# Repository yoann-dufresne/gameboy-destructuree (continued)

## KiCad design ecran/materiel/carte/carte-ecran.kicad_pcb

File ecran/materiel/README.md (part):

# Matériel de l'écran 3 × 3 — le montage définitif

*Conçu le 29/10/2026.* L'écran fonctionne ; son montage de preuve de concept a fait son
office. Ce dossier le remplace par un montage qu'on peut poser à plat sur le sol, mettre
debout sur une table, accrocher au mur, et dépanner sans démonter : **une carte** où s'enfichent les quatre Pico et toutes les
nappes, **un cadre** en profilés aluminium 2020 et pièces imprimées, **un faisceau**
d'alimentation propre, du secteur à chaque dalle.

**État : conçu et vérifié par calcul ; cartes reçues de JLCPCB le 05/11/2026, à monter.** La
carte passe les contrôles électriques de KiCad sans une erreur ; le cadre passe ses contrôles
d'interférences et d'accès. Ce qui reste à vérifier sur pièce est listé au [§8](#8-limites-et-points-à-vérifier).
Le montage de la carte, étape par étape et éprouvé à chaque étape :
[`montage-carte.md`](montage-carte.md).

**Ce qu'il faut acheter : [`liste-materiel.md`](liste-materiel.md)**, de l'ordre de 250 à
350 €, hors dalles, Pico et alimentation, déjà là.

---

## 1. Ce qui change

| Sur le montage de preuve de concept | Dans le montage définitif |
|---|---|
| Les dalles s'affaissent : des plaques de PLA les tiennent entre elles, et le PLA flue sous le poids | Chaque rangée est vissée sur un **profilé aluminium 2020**, et les trois profilés sur **deux montants 2020**. L'aluminium porte, le plastique ne fait plus que relier |
| Des fils volants au dos | **Une carte** : les 4 Pico sur supports, les liaisons tête → nœuds en pistes, les tampons de niveaux, les 3 embases HUB75, les 9 départs d'alimentation |
| Plusieurs cosses écrasées ensemble sur chaque borne de l'alimentation | **Un câble par dalle**, protégé par **son fusible** et débrochable à la carte ; de l'alimentation à la carte, **quatre fils de 2,5 mm², un par borne** |
| Les Pico alimentés par USB | Les Pico **tirent leur 5 V du même bus**, à travers un fusible réarmable, une ferrite et une diode Schottky par Pico. L'USB reste branchable pour flasher : aucun des deux n'alimente l'autre |
| Ni pied ni accroche | **Quatre patins arrière**, toujours en place : l'écran se pose **à plat sur le sol**, LED vers le haut, ou s'accroche au mur par **deux crochets** à trou de serrure. **Deux pieds** amovibles le tiennent debout sur une table, droit ou penché de 10° |
| Les connecteurs des dalles difficiles à atteindre | **Rien** — cadre, carte, alimentation, câbles — au-dessus d'un connecteur de dalle ni à moins de 8 mm, jusqu'au plan du mur. Le générateur du cadre le vérifie à chaque exécution |

Le firmware ne change pas d'une ligne : la carte reprend les brochages des `config.h` de
la tête et des nœuds.

---

## 2. Vue d'ensemble

Vue de dos, flèches des dalles vers le haut, numérotation du cadre v3 :

```
   7 8 9   ← nœud 0 (U2), nappe J4 → entrée de la dalle 7      crochets muraux sur ce profilé
   4 5 6   ← nœud 1 (U3), nappe J5 → dalle 4   ┐ la carte, sur les dalles 4 et 5
   1 2 3   ← nœud 2 (U4), nappe J6 → dalle 1   ┘ l'alimentation, sur le profilé du bas
           4 patins arrière au bout des montants ; pieds de table sous le profilé du bas ;
           prise secteur à gauche
```

| | |
|---|---|
| Encombrement | 576 × 576 mm ; 120 mm de la face des LED au sol, ou au mur |
| À plat sur le sol | sur les 4 patins arrière, rectangle d'appui de 384 × 340 mm ; centre de gravité à 131 mm de son bord |
| Debout, sur une table | écran à 25 mm de la table ; patins des pieds de 240 mm, qui dépassent de 35 mm devant |
| Masse | environ 7,5 kg, estimée pièce par pièce : dalles ≈ 4,5 kg, alimentation ≈ 0,7 kg, cadre et carte ≈ 2,3 kg |
| Alimentation | une seule, **5 V 30 A**, sur le profilé du bas ; secteur par une embase IEC à interrupteur et fusible |

---

## 3. La carte — [`carte/`](carte/)

**198 × 135 mm, 2 couches, cuivre 2 oz.** Elle se visse sur un plateau imprimé, lui-même
vissé au profilé de la rangée du milieu, une patte appuyée contre le montant gauche.

| Repère | Rôle |
|---|---|
| **J1** | entrée 5 V 30 A, bornier à vis : bornes 1-2 = +5 V, 3-4 = masse. Deux fils de 2,5 mm² par polarité |
| **F1–F9, J11–J19** | les 9 départs, un par dalle : fusible lame mini **7,5 A** et fiche débrochable au pas de 5,08 mm. Repérés D1 à D9 sur la sérigraphie |
| LED11–LED19 | voyant rouge d'un départ : **allumé = fusible fondu**, dalle branchée |
| LED1 | voyant vert : le 5 V est là |
| **U1** | la tête, Pico 2 W, USB en haut, antenne au bord bas de la carte, sans cuivre dessous |
| **U2–U4** | les nœuds 0, 1 et 2 (rangées du haut, du milieu, du bas), Pico 2, USB à droite |
| **J4, J5, J6** | embases HUB75 vers l'entrée des dalles 7, 4 et 1 |
| U5–U10 | deux tampons **74AHCT541** par nœud, alimentés en 5 V : niveaux 5 V vers les dalles, Pico protégés. Leurs entrées n'ont pas de diode vers l'alimentation : un nœud branché en USB, bus éteint, ne réalimente pas la carte. Validés par le 3V3 de leur Pico (Q1–Q3) : **sans Pico, la rangée reste noire**, même tête en marche |
| JP1–JP3 | G1 de chaque nœud : cavalier sur 1-2 = GP1, la normale ; sur 2-3 = GP15, pour un Pico dont la sortie GP1 est morte (journal du 29/10/2026) |
| SW1–SW4 | RESET de la tête et des trois nœuds |
| J7 | sonde pour analyseur logique : VSYNC, RDY0–2, GP17 et GP18 de chaque Pico, une masse par signal |
| J2, J3 | potentiomètre de luminosité sur GP26 de la tête (option, non lu par le firmware) ; broches libres de la tête |

- **Liaisons tête → nœuds** : en pistes, avec les résistances série de 33 Ω du [§2.6 du
  plan](../docs/plan-firmware.md). Les nappes IDC 10 points disparaissent.
- **5 V des Pico** : fusible réarmable 0,75 A, ferrite, condensateurs, puis une diode SS14
  vers le VSYS de chaque Pico.
- **Mesure du bus** : un pont diviseur ramène le 5 V à 2,5 V sur GP27 (ADC1) de la tête.
  Câblé, pas encore lu par le firmware.

**Fabrication** — tout est dans [`carte/fab/`](carte/fab/). Le zip ne contient que la
**carte nue**, Gerber et perçages. Le **peuplement** est dans deux fichiers à part, qu'on
téléverse à l'étape d'assemblage de la commande :

| Fichier | Usage |
|---|---|
| `carte-ecran-gerber.zip` | la carte nue, à déposer tel quel chez JLCPCB |
| `bom_jlcpcb.csv`, `cpl_jlcpcb.csv` | le peuplement : nomenclature, avec les codes LCSC, et placement des 93 CMS de la face dessus |
| `nomenclature.md` | toutes les pièces de la carte, CMS, traversants et vrac |
| `schema.pdf`, `plan_montage.pdf`, `cuivre_dessus.pdf`, `cuivre_dessous.pdf` | pour souder et dépanner |

**Commander chez JLCPCB :**

1. Déposer `carte-ecran-gerber.zip`. Options : 2 couches, 1,6 mm, **cuivre extérieur 2 oz**,
   HASL sans plomb, 5 cartes.
2. Activer **PCB Assembly**, face dessus, 2 cartes à peupler. Téléverser `bom_jlcpcb.csv`,
   puis `cpl_jlcpcb.csv`.
3. Vérifier que les 16 références LCSC sont reconnues et en stock, puis, dans l'aperçu,
   **l'orientation** des pièces polarisées : [`fab/orientation_cms.png`](carte/fab/orientation_cms.png)
   marque en rouge le repère de chacune (cathode des LED et des SS14, + de C4, broche 1 des
   74AHCT541, patte seule des 2N7002, cathode de D1). Les bibliothèques de JLCPCB ne tournent pas toutes
   comme celles de KiCad : `cpl_jlcpcb.csv` corrige déjà les TSSOP (+270°), les SOT-23 (+180°)
   et les réseaux de résistances (+90°), d'après l'aperçu du 29/10/2026. Dans l'aperçu, le
   point rose des 74AHCT541 doit tomber en bas à droite, contre le ◁ de la sérigraphie.
4. Les traversants n'en font pas partie : supports des Pico, embases HUB75, porte-fusibles,
   borniers, C1 et C2, boutons, barrettes. Ils s'achètent à part, au §1b de la
   [liste de matériel](liste-materiel.md), et se soudent à la main.

Contrôles passés : ERC sans erreur, netlist identique à la description, routage complet,
DRC sans violation, aucune connexion manquante, schéma et circuit concordants.

**Vérifications avant commande (29/10/2026)** :

| Point | Résultat |
|---|---|
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
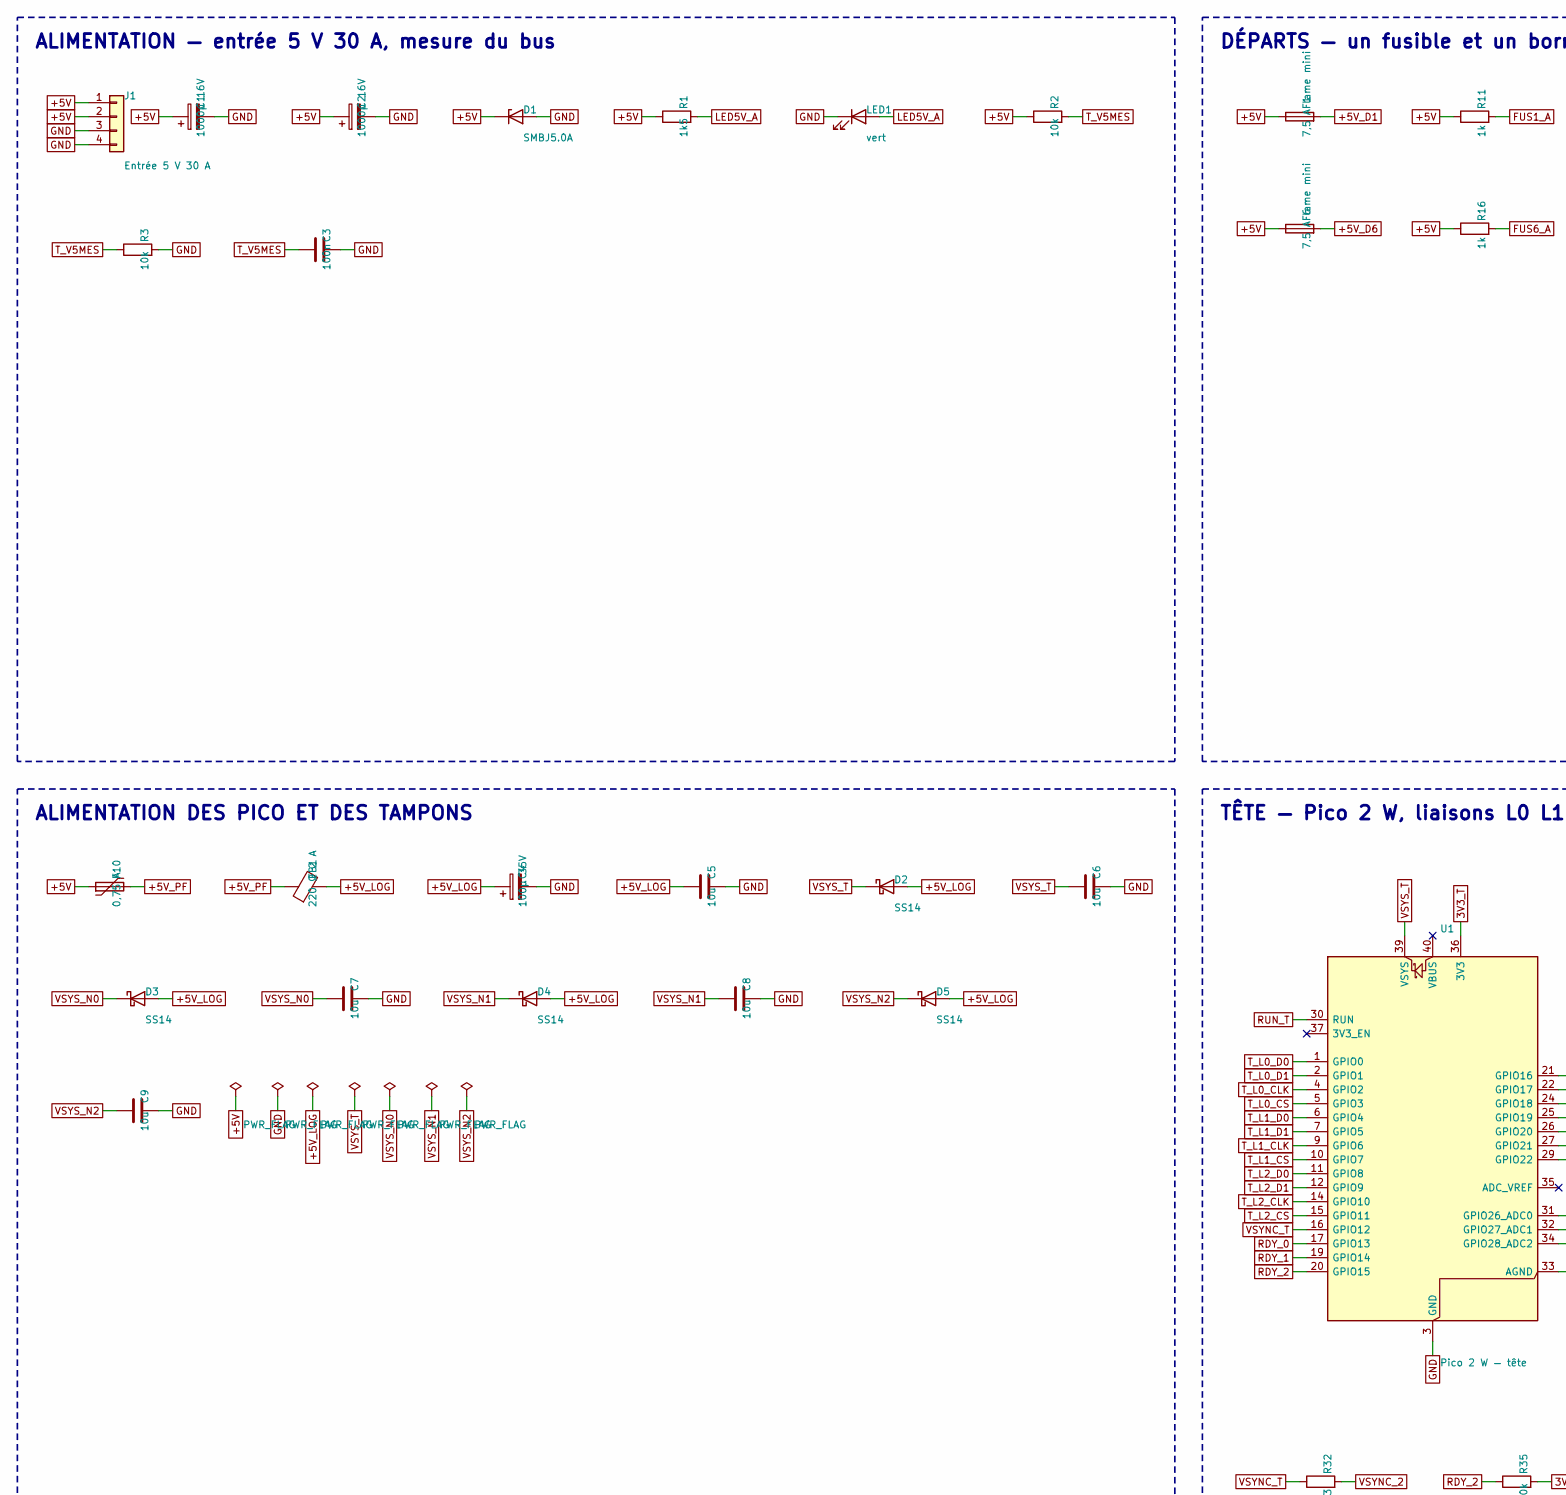
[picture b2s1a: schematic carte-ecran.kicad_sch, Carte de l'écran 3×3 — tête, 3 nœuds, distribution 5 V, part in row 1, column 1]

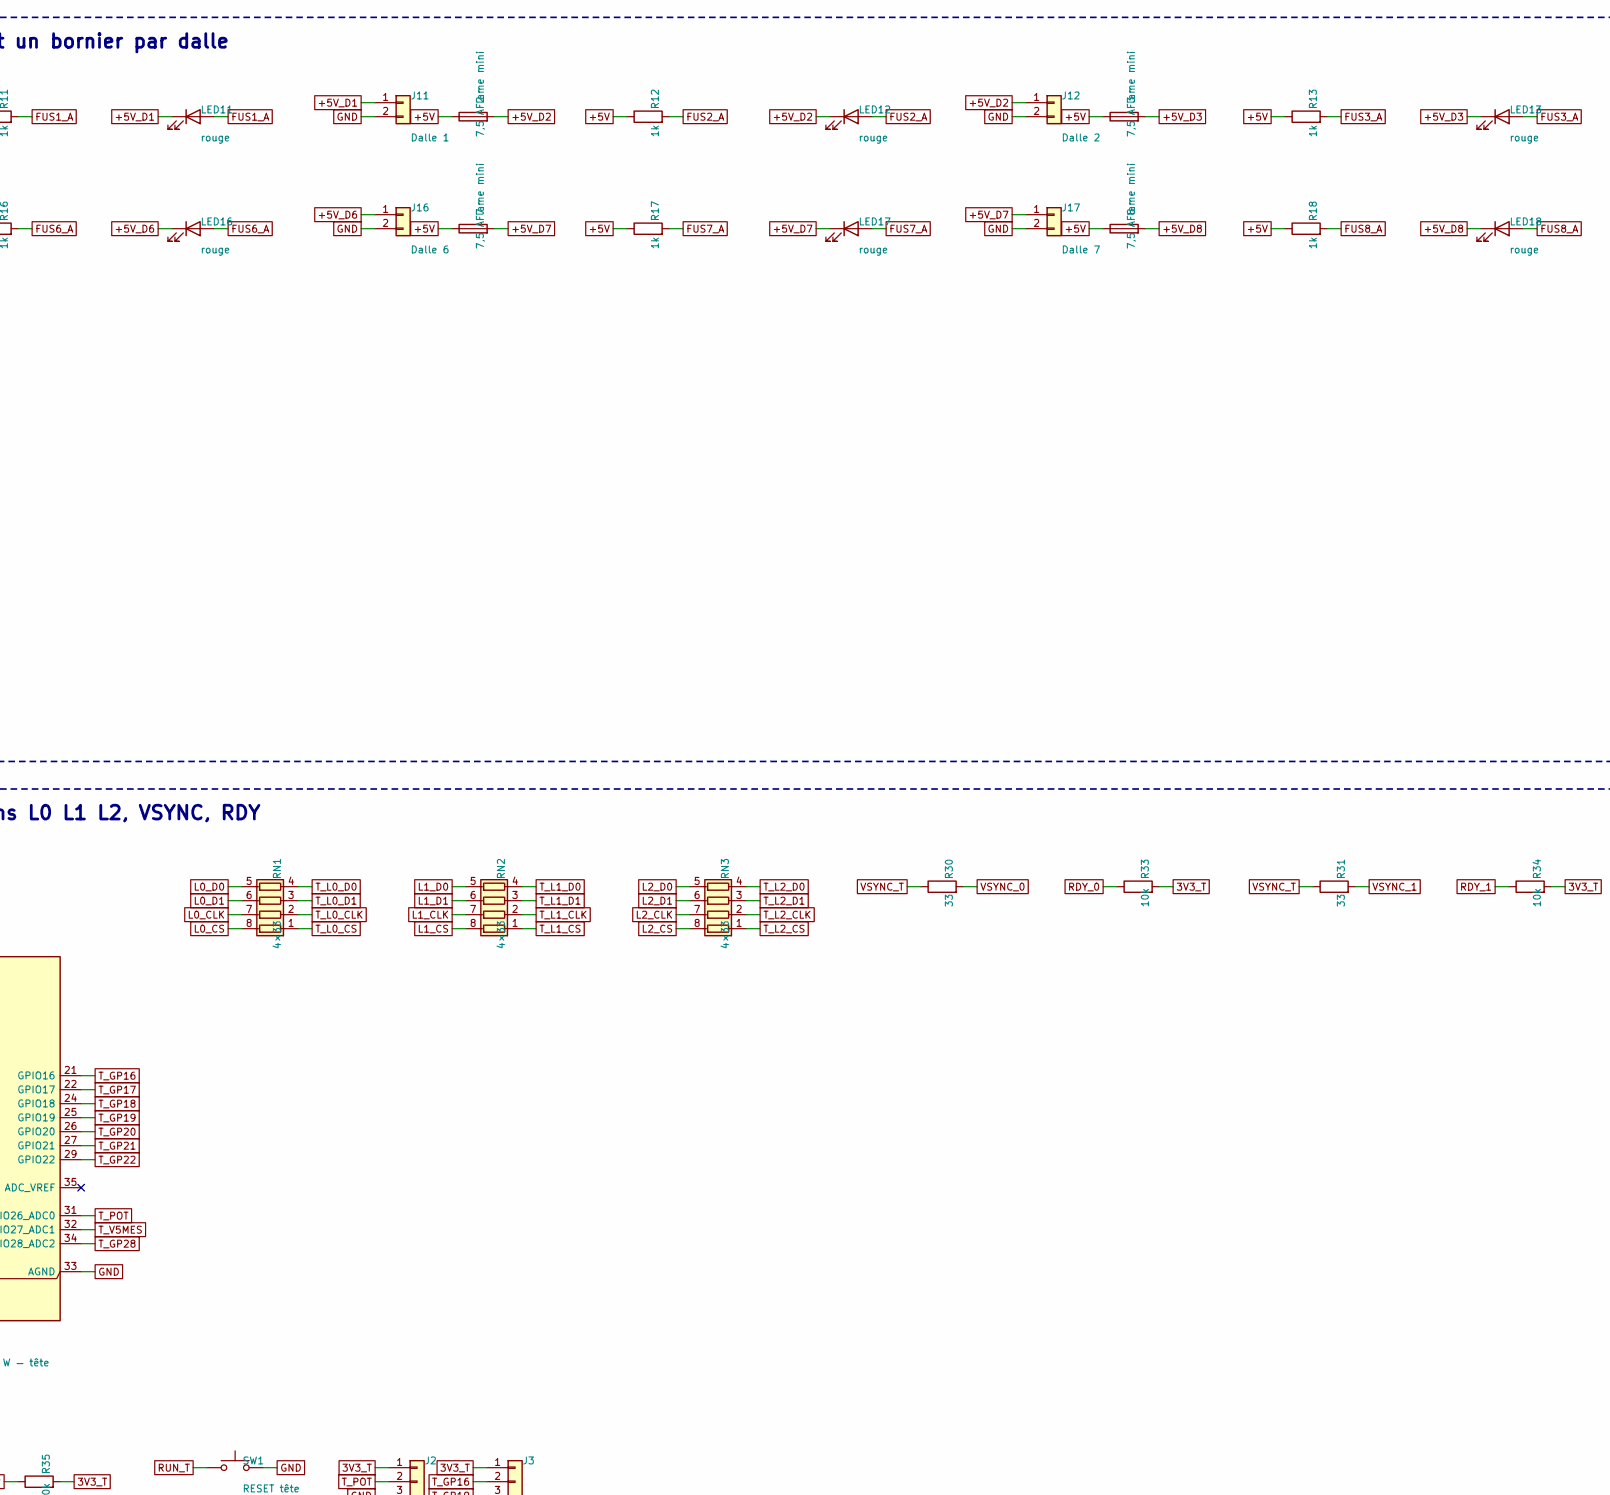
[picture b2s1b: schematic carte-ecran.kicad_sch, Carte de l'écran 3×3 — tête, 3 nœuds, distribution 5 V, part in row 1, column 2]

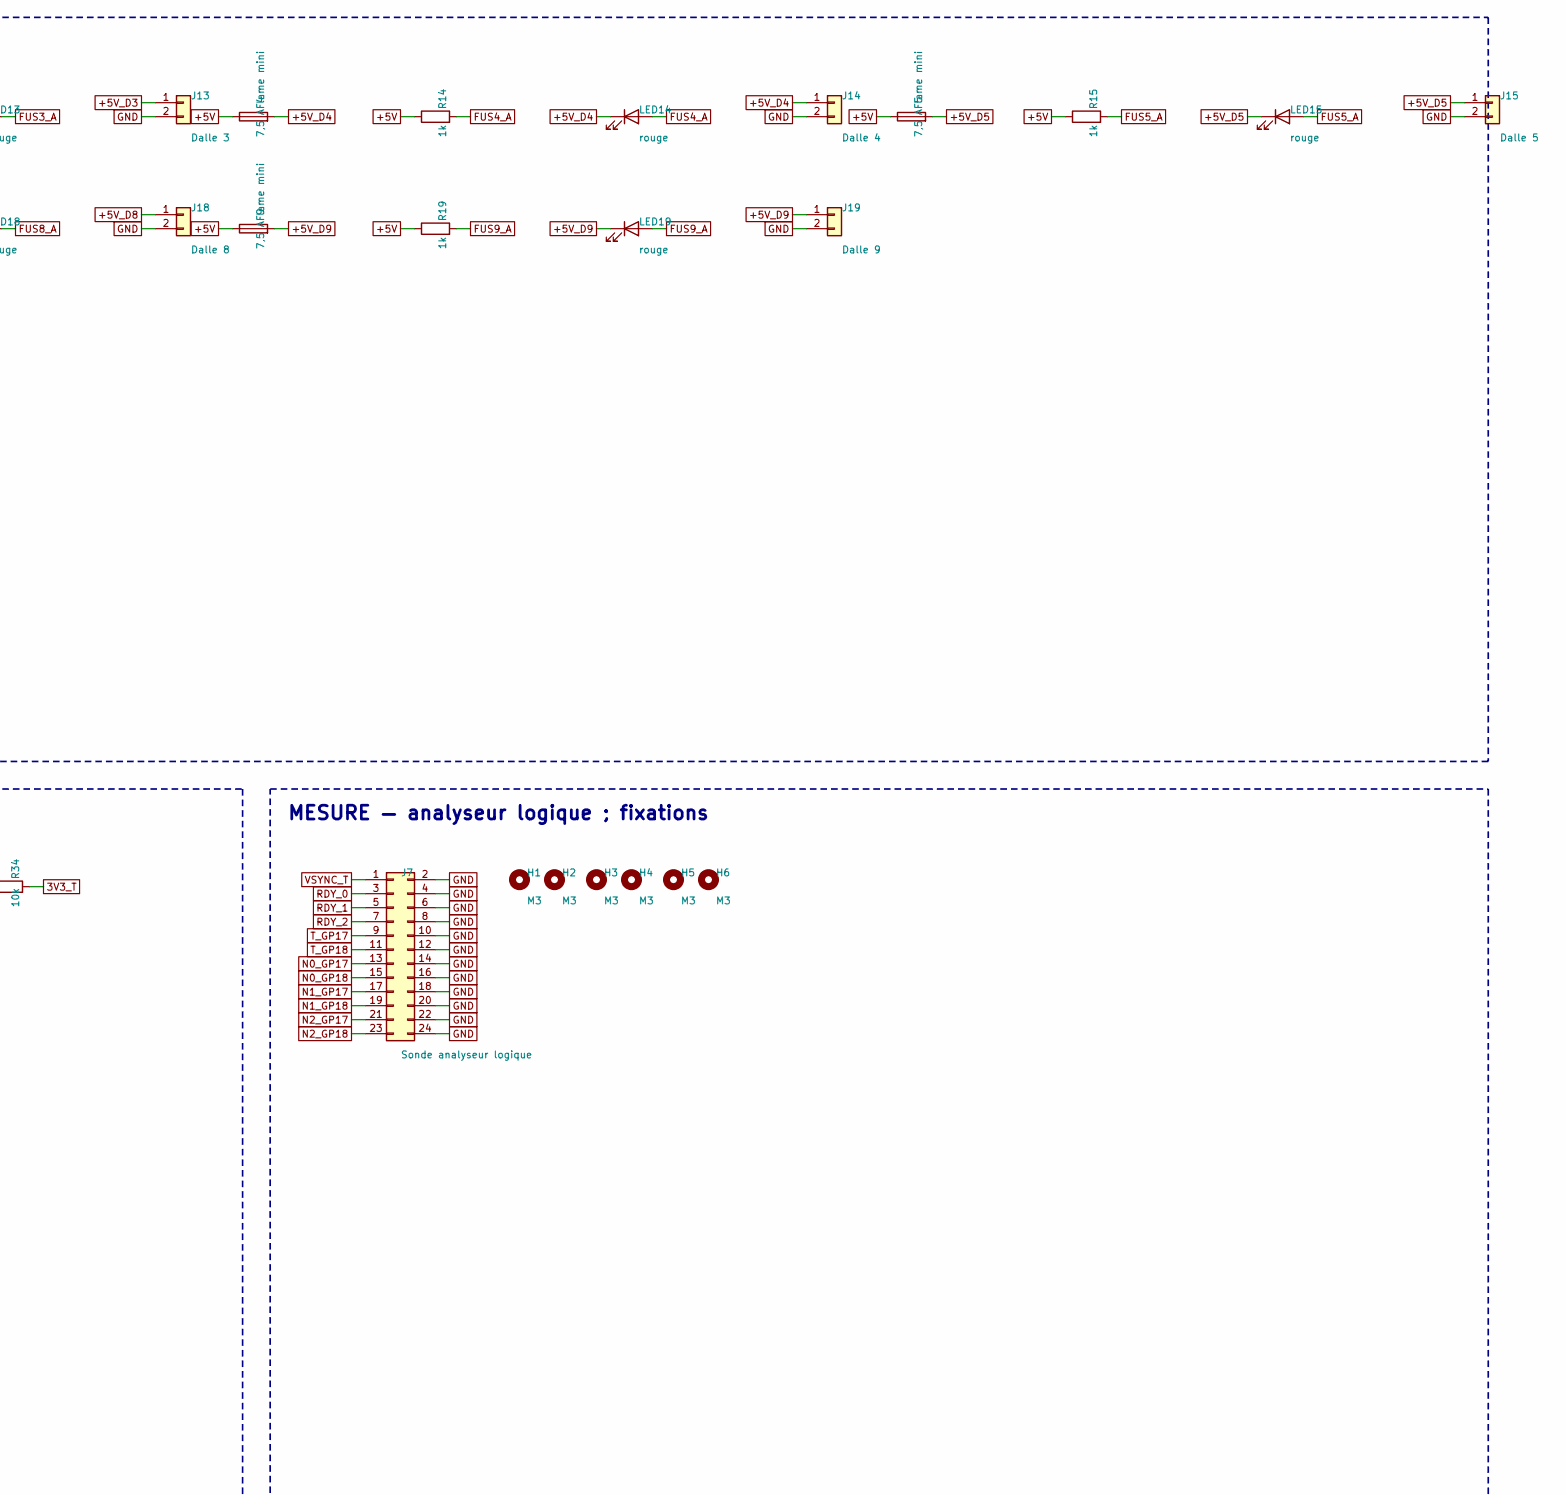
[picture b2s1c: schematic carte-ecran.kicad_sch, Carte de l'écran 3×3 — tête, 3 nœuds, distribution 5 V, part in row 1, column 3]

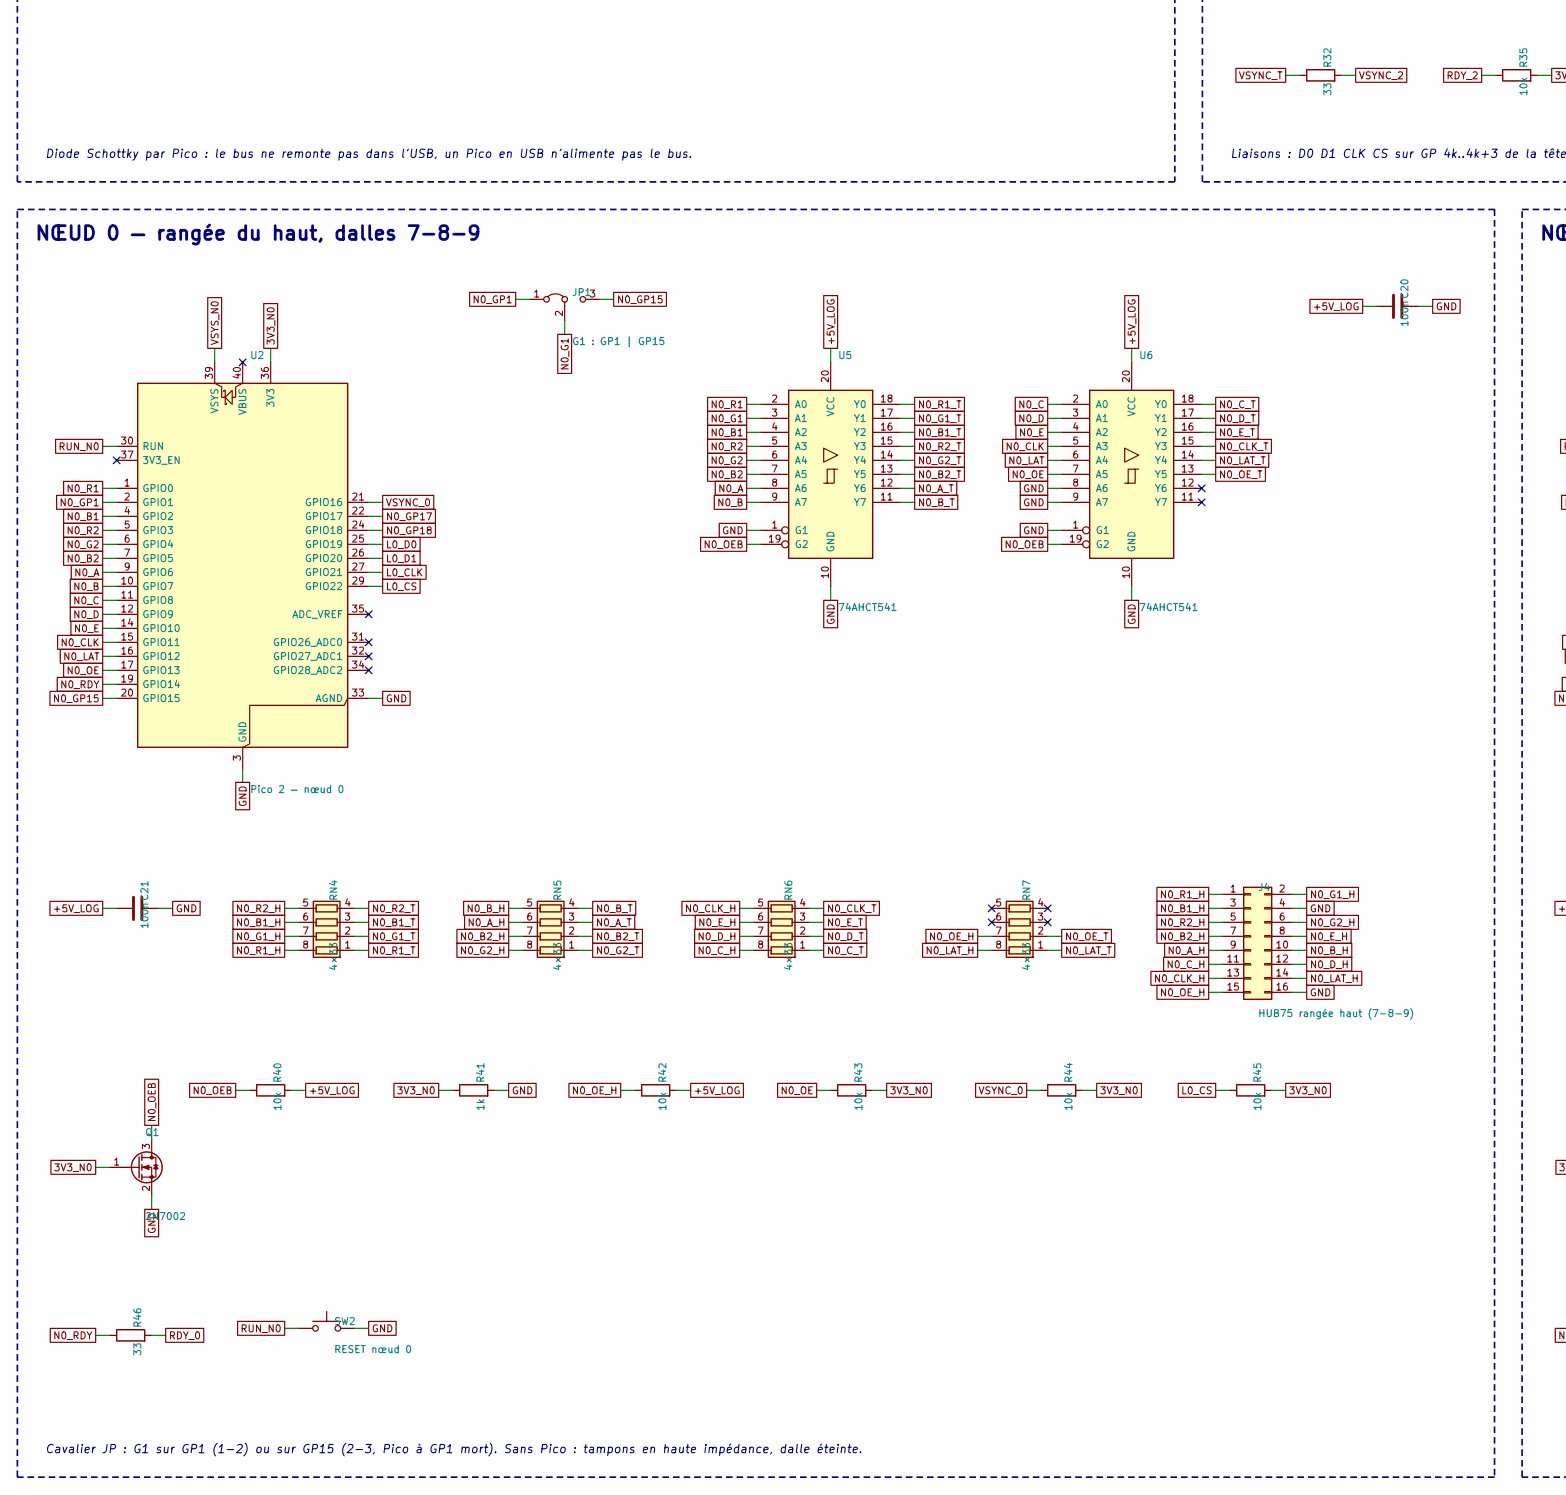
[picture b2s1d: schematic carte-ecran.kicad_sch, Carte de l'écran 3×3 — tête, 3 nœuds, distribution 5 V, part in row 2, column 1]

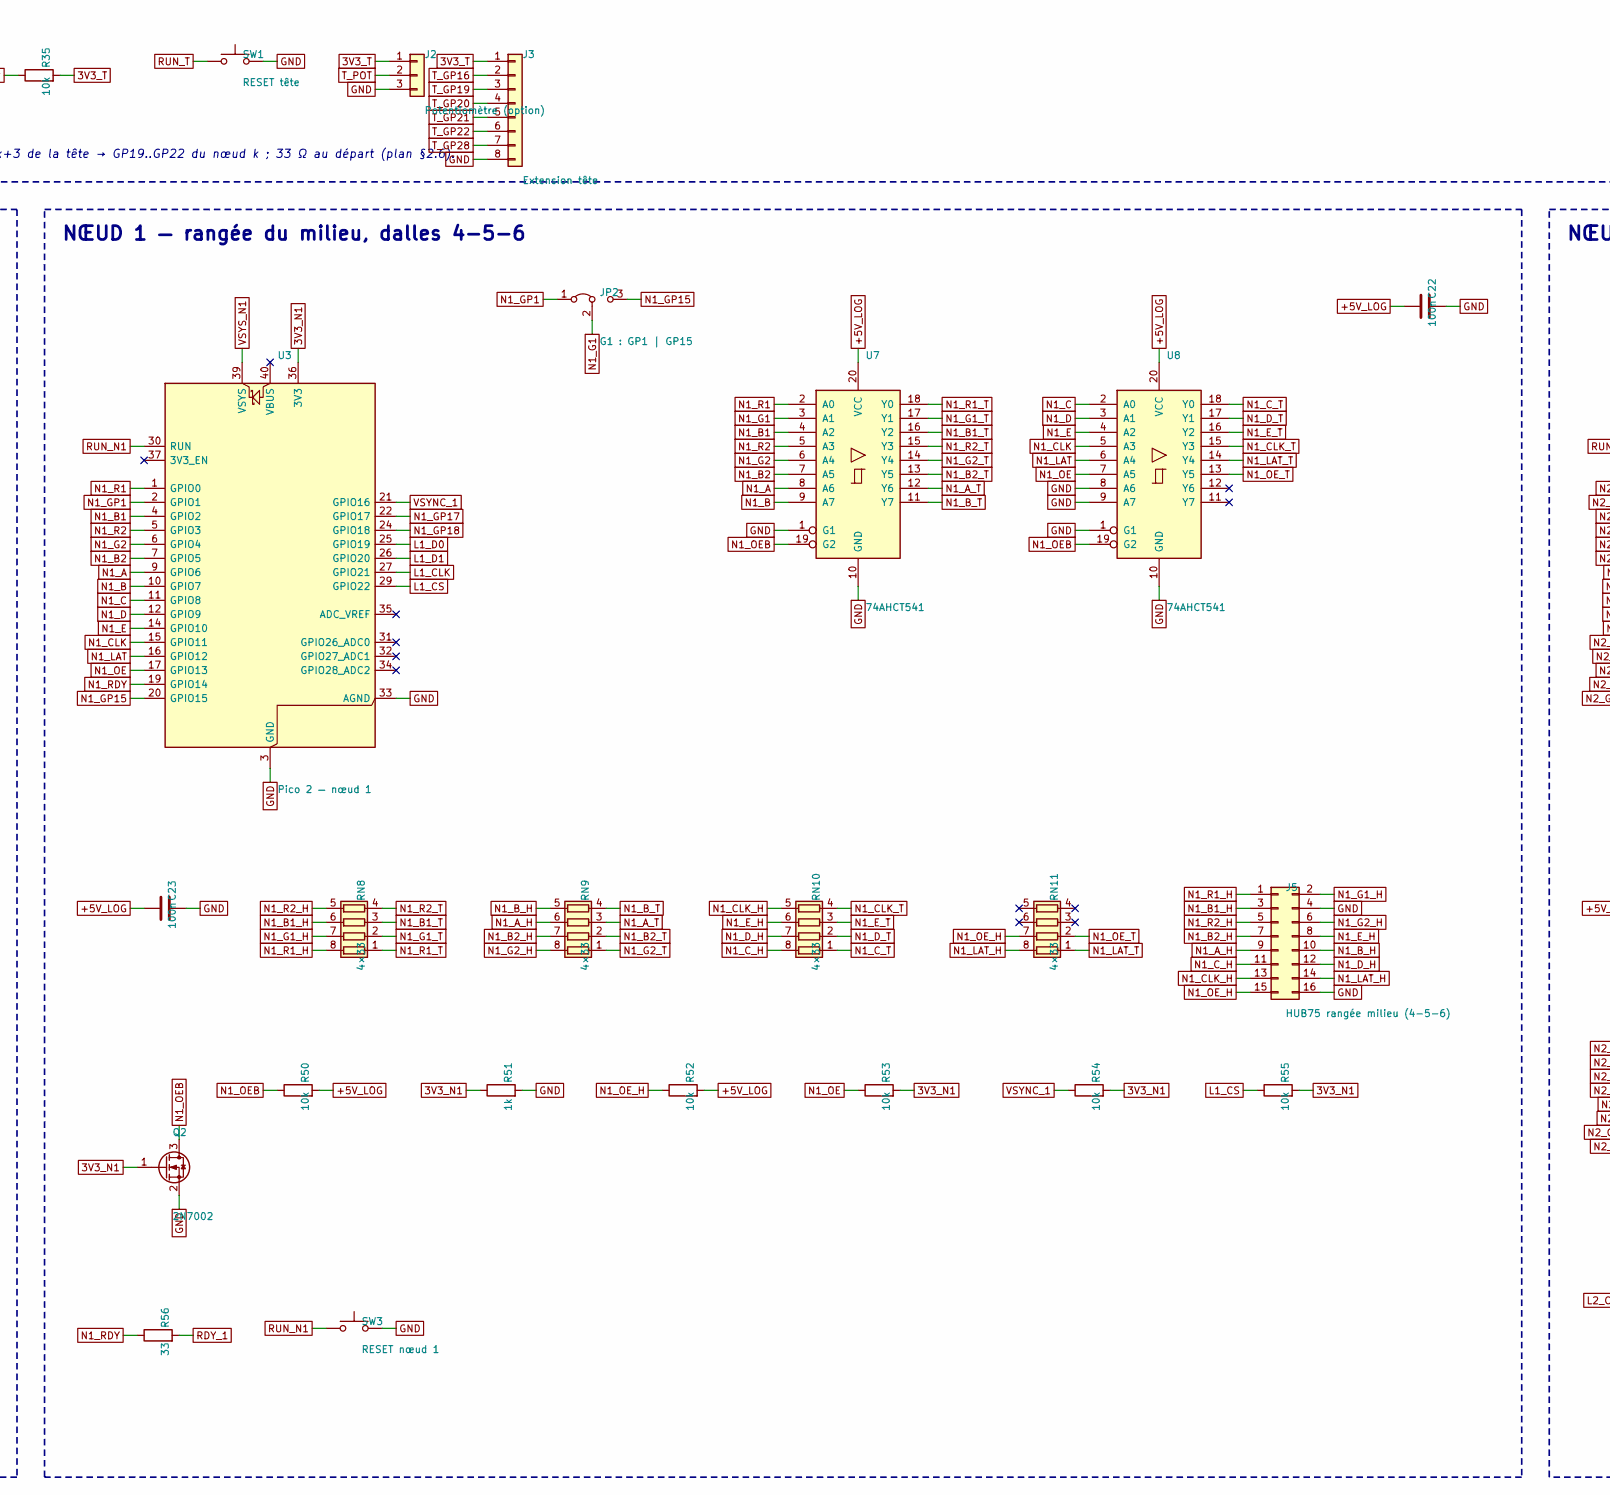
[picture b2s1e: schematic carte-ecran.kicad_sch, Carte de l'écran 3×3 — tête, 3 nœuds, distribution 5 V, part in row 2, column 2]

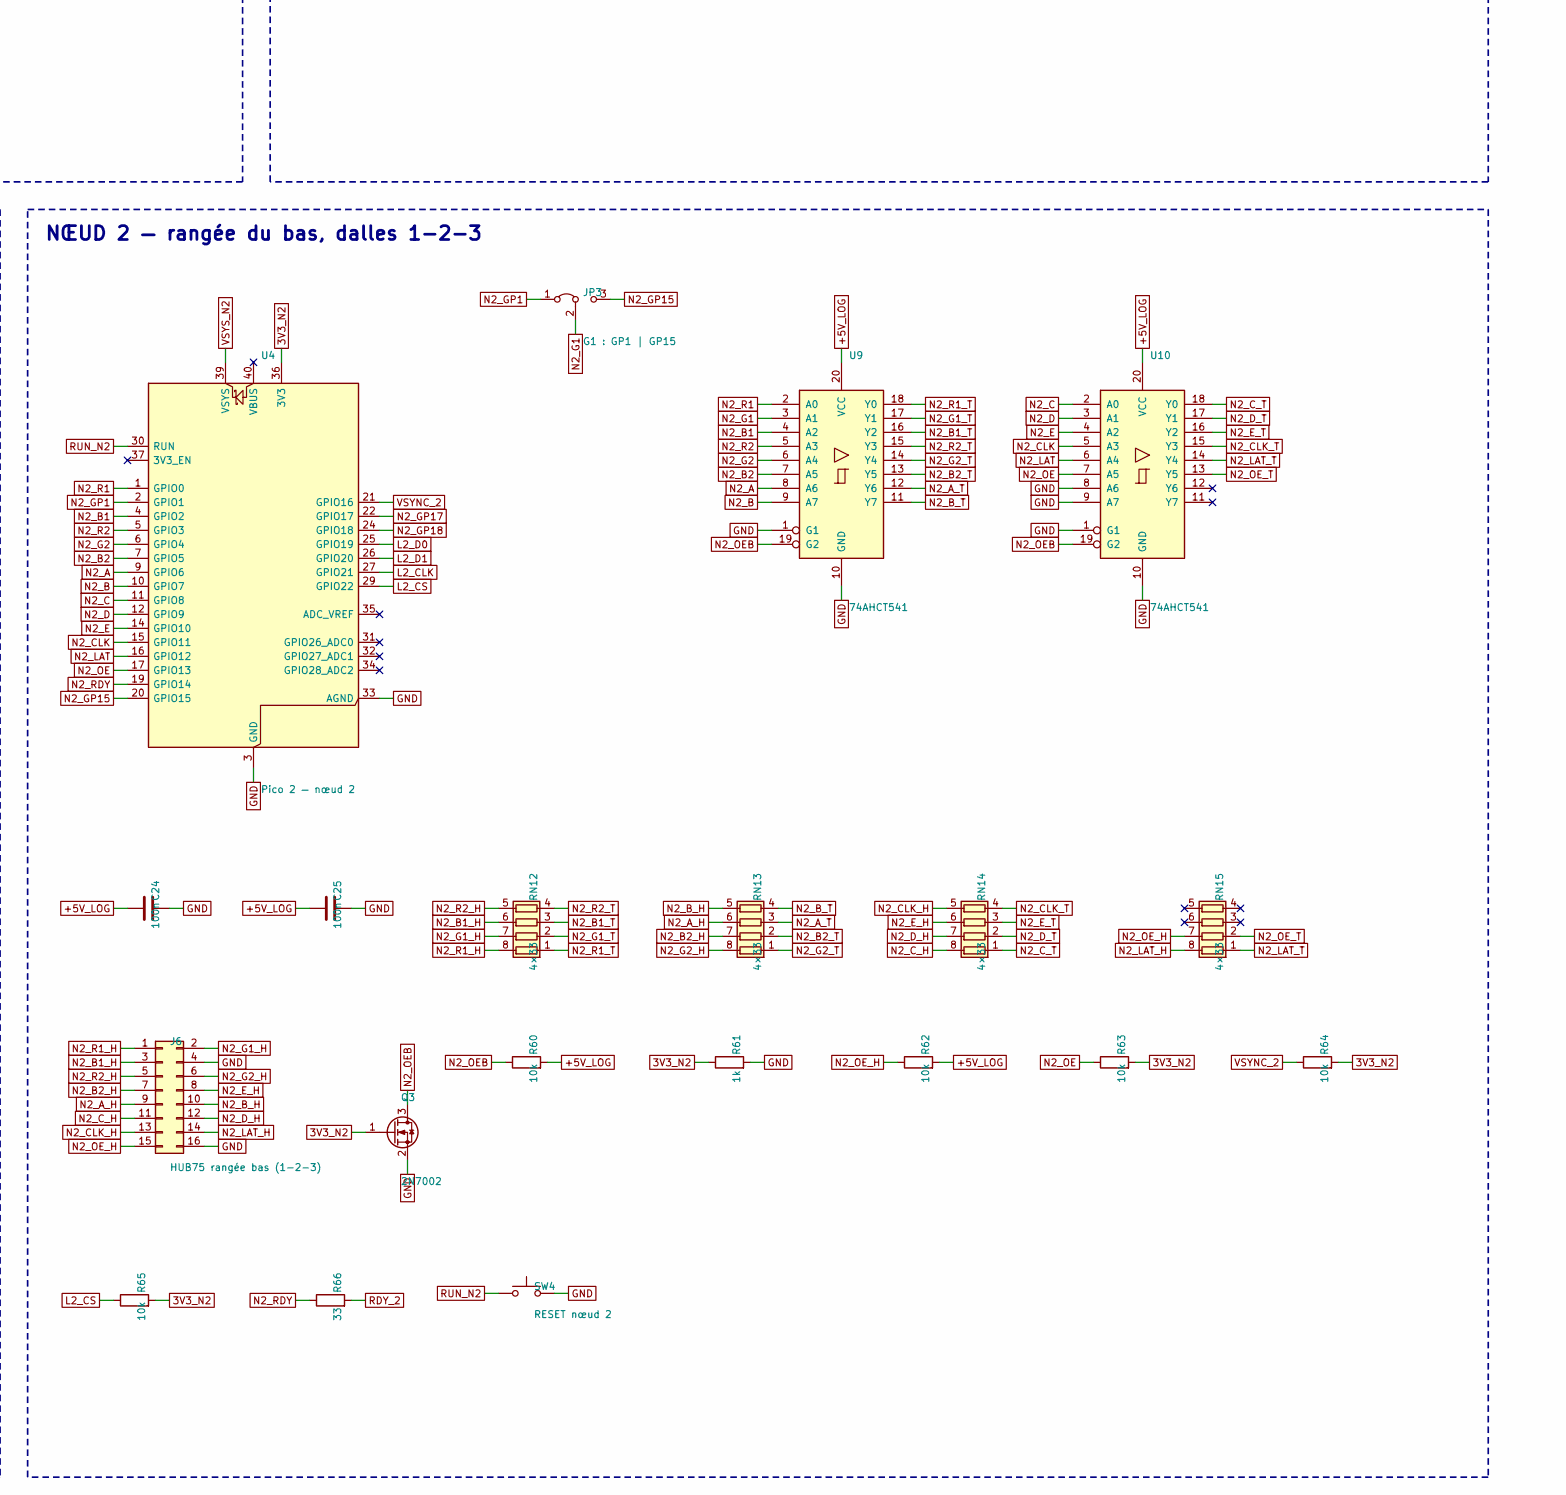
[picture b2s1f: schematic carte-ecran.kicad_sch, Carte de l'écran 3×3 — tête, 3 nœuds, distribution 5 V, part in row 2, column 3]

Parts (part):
C1, C2: 1000µ 16V; CP_Radial_D10.0mm_P5.00mm; MPN 1000 µF 16 V radial Ø10 × 20, pas de 5 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
C3, C20, C21, C22, C23, C24, C25: 100n; C_0603_1608Metric; MPN CC0603KRX7R9BB104; LCSC C14663
C4: 100µ 35V; CP_Elec_6.3x7.7; MPN CK1V101M-CRE77 (100 µF 35 V, 6,3×7,7); LCSC C19184138
C5, C6, C7, C8, C9: 10u; C_0805_2012Metric; MPN CL21A106KAYNNNE; LCSC C15850
D1: SMBJ5.0A; D_SMB; MPN SMBJ5.0A (Littelfuse, unidirectionnelle); LCSC C83333
D2, D3, D4, D5: SS14; D_SMA; MPN SS14; LCSC C2480
F1, F2, F3, F4, F5, F6, F7, F8, F9: 7,5 A lame mini; Fuseholder_Blade_Mini_Keystone_3568; MPN Keystone 3568 (porte-fusible lame mini 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
F10: 0,75 A; Fuse_1812_4532Metric; MPN 1812L075/33DR (Littelfuse, 0,75 A maint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; LCSC C151170
FB1: 220 Ω 2 A; L_0805_2012Metric; MPN BLM21PG221SN1D (220 Ω à 100 MHz, 2 A); LCSC C85840
H1, H2, H3, H4, H5, H6: M3; MountingHole_3.2mm_M3
J1: Entrée 5 V 30 A; TerminalBlock_Phoenix_MKDS-3-4-5.08_1x04_P5.08mm_Horizontal; MPN Phoenix MKDS 3/4-5,08 (1712805), 24 A p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
J2: Potentiomètre (option); PinHeader_1x03_P2.54mm_Vertical; MPN Barrette mâle 2,54 mm
J3: Extension tête; PinHeader_1x08_P2.54mm_Vertical; MPN Barrette mâle 2,54 mm
J4: HUB75 rangée haut (7-8-9); IDC-Header_2x08_P2.54mm_Vertical; MPN Embase IDC 2×8 détrompée, 2,54 mm, droi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
J5: HUB75 rangée milieu (4-5-6); IDC-Header_2x08_P2.54mm_Vertical; MPN Embase IDC 2×8 détrompée, 2,54 mm, droi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
J6: HUB75 rangée bas (1-2-3); IDC-Header_2x08_P2.54mm_Vertical; MPN Embase IDC 2×8 détrompée, 2,54 mm, droi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
J7: Sonde analyseur logique; PinHeader_2x12_P2.54mm_Vertical; MPN Barrette mâle 2,54 mm
J11: Dalle 1; PhoenixContact_MSTBA_2,5_2-G-5,08_1x02_P5.08mm_Horizontal; MPN Phoenix MSTBA 2,5/2-G-5,08 (1757242) + 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
J12: Dalle 2; PhoenixContact_MSTBA_2,5_2-G-5,08_1x02_P5.08mm_Horizontal; MPN Phoenix MSTBA 2,5/2-G-5,08 (1757242) + 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
J13: Dalle 3; PhoenixContact_MSTBA_2,5_2-G-5,08_1x02_P5.08mm_Horizontal; MPN Phoenix MSTBA 2,5/2-G-5,08 (1757242) + 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
J14: Dalle 4; PhoenixContact_MSTBA_2,5_2-G-5,08_1x02_P5.08mm_Horizontal; MPN Phoenix MSTBA 2,5/2-G-5,08 (1757242) + 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
J15: Dalle 5; PhoenixContact_MSTBA_2,5_2-G-5,08_1x02_P5.08mm_Horizontal; MPN Phoenix MSTBA 2,5/2-G-5,08 (1757242) + 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
J16: Dalle 6; PhoenixContact_MSTBA_2,5_2-G-5,08_1x02_P5.08mm_Horizontal; MPN Phoenix MSTBA 2,5/2-G-5,08 (1757242) + 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
J17: Dalle 7; PhoenixContact_MSTBA_2,5_2-G-5,08_1x02_P5.08mm_Horizontal; MPN Phoenix MSTBA 2,5/2-G-5,08 (1757242) + 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
J18: Dalle 8; PhoenixContact_MSTBA_2,5_2-G-5,08_1x02_P5.08mm_Horizontal; MPN Phoenix MSTBA 2,5/2-G-5,08 (1757242) + 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
J19: Dalle 9; PhoenixContact_MSTBA_2,5_2-G-5,08_1x02_P5.08mm_Horizontal; MPN Phoenix MSTBA 2,5/2-G-5,08 (1757242) + 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
JP1, JP2, JP3: G1 : GP1 | GP15; PinHeader_1x03_P2.54mm_Vertical; MPN Barrette mâle 2,54 mm
LED1: vert; LED_0603_1608Metric; MPN XL-1608PGC-06 (XINGLIGHT, vert émeraude); LCSC C7371905
LED11, LED12, LED13, LED14, LED15, LED16, LED17, LED18, LED19: rouge; LED_0603_1608Metric; MPN KT-0603R; LCSC C2286
PF1, PF2, PF3, PF4, PF5, PF6, PF7: PWR_FLAG
Q1, Q2, Q3: 2N7002; SOT-23; MPN 2N7002; LCSC C8545
R1: 1k5; R_0603_1608Metric; MPN 0603WAF1501T5E; LCSC C22843
R2, R3, R33, R34, R35, R40, R42, R43, R44, R45, R50, R52, R53, R54, R55, R60, R62, R63, R64, R65: 10k; R_0603_1608Metric; MPN 0603WAF1002T5E; LCSC C25804
R11, R12, R13, R14, R15, R16, R17, R18, R19, R41, R51, R61: 1k; R_0603_1608Metric; MPN 0603WAF1001T5E; LCSC C21190
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
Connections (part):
3V3_N0: Q1.1 (G), R41.1, R43.2, R44.2, R45.2, U2.36 (3V3)
3V3_N1: Q2.1 (G), R51.1, R53.2, R54.2, R55.2, U3.36 (3V3)
3V3_N2: Q3.1 (G), R61.1, R63.2, R64.2, R65.2, U4.36 (3V3)
3V3_T: J2.1, J3.1, R33.2, R34.2, R35.2, U1.36 (3V3)
+5V: C1.1, C2.1, D1.1 (K), F1.1, F2.1, F3.1, F4.1, F5.1, F6.1, F7.1, F8.1, F9.1, F10.1, J1.1, J1.2, PF1.1, R1.1, R2.1, R11.1, R12.1, R13.1, R14.1, R15.1, R16.1, R17.1, R18.1, R19.1
+5V_D1: F1.2, J11.1, LED11.1 (K)
+5V_D2: F2.2, J12.1, LED12.1 (K)
+5V_D3: F3.2, J13.1, LED13.1 (K)
+5V_D4: F4.2, J14.1, LED14.1 (K)
+5V_D5: F5.2, J15.1, LED15.1 (K)
+5V_D6: F6.2, J16.1, LED16.1 (K)
+5V_D7: F7.2, J17.1, LED17.1 (K)
+5V_D8: F8.2, J18.1, LED18.1 (K)
+5V_D9: F9.2, J19.1, LED19.1 (K)
+5V_LOG: C4.1, C5.1, C20.1, C21.1, C22.1, C23.1, C24.1, C25.1, D2.2 (A), D3.2 (A), D4.2 (A), D5.2 (A), FB1.2, PF3.1, R40.2, R42.2, R50.2, R52.2, R60.2, R62.2, U5.20 (VCC), U6.20 (VCC), U7.20 (VCC), U8.20 (VCC), U9.20 (VCC), U10.20 (VCC)
+5V_PF: F10.2, FB1.1
FUS1_A: LED11.2 (A), R11.2
FUS2_A: LED12.2 (A), R12.2
FUS3_A: LED13.2 (A), R13.2
FUS4_A: LED14.2 (A), R14.2
FUS5_A: LED15.2 (A), R15.2
FUS6_A: LED16.2 (A), R16.2
FUS7_A: LED17.2 (A), R17.2
FUS8_A: LED18.2 (A), R18.2
FUS9_A: LED19.2 (A), R19.2
GND: C1.2, C2.2, C3.2, C4.2, C5.2, C6.2, C7.2, C8.2, C9.2, C20.2, C21.2, C22.2, C23.2, C24.2, C25.2, D1.2 (A), J1.3, J1.4, J2.3, J3.8, J4.4, J4.16, J5.4, J5.16, J6.4, J6.16, J7.2, J7.4, J7.6, J7.8, J7.10, J7.12, J7.14, J7.16, J7.18, J7.20, J7.22, J7.24, J11.2, J12.2, J13.2, J14.2, J15.2, J16.2, J17.2, J18.2, J19.2, LED1.1 (K), PF2.1, Q1.2 (S), Q2.2 (S), Q3.2 (S), R3.2, R41.2, R51.2, R61.2, SW1.2, SW2.2, SW3.2, SW4.2, U1.3 (GND), U1.8 (GND), U1.13 (GND), U1.18 (GND), U1.23 (GND), U1.28 (GND), U1.33 (AGND), U1.38 (GND), U2.3 (GND), U2.8 (GND), U2.13 (GND), U2.18 (GND), U2.23 (GND), U2.28 (GND), U2.33 (AGND), U2.38 (GND), U3.3 (GND), U3.8 (GND), U3.13 (GND), U3.18 (GND)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
L0_CLK: RN1.7 (R2.2), U2.27 (GPIO21)
L0_CS: R45.1, RN1.8 (R1.2), U2.29 (GPIO22)
L0_D0: RN1.5 (R4.2), U2.25 (GPIO19)
L0_D1: RN1.6 (R3.2), U2.26 (GPIO20)
L1_CLK: RN2.7 (R2.2), U3.27 (GPIO21)
L1_CS: R55.1, RN2.8 (R1.2), U3.29 (GPIO22)
L1_D0: RN2.5 (R4.2), U3.25 (GPIO19)
L1_D1: RN2.6 (R3.2), U3.26 (GPIO20)
L2_CLK: RN3.7 (R2.2), U4.27 (GPIO21)
L2_CS: R65.1, RN3.8 (R1.2), U4.29 (GPIO22)
L2_D0: RN3.5 (R4.2), U4.25 (GPIO19)
L2_D1: RN3.6 (R3.2), U4.26 (GPIO20)
LED5V_A: LED1.2 (A), R1.2
N0_A: U2.9 (GPIO6), U5.8 (A6)
N0_A_H: J4.9, RN5.6 (R3.2)
N0_A_T: RN5.3 (R3.1), U5.12 (Y6)
N0_B: U2.10 (GPIO7), U5.9 (A7)
N0_B1: U2.4 (GPIO2), U5.4 (A2)
N0_B1_H: J4.3, RN4.6 (R3.2)
N0_B1_T: RN4.3 (R3.1), U5.16 (Y2)
N0_B2: U2.7 (GPIO5), U5.7 (A5)
N0_B2_H: J4.7, RN5.7 (R2.2)
N0_B2_T: RN5.2 (R2.1), U5.13 (Y5)
N0_B_H: J4.10, RN5.5 (R4.2)
N0_B_T: RN5.4 (R4.1), U5.11 (Y7)
N0_C: U2.11 (GPIO8), U6.2 (A0)
N0_CLK: U2.15 (GPIO11), U6.5 (A3)
N0_CLK_H: J4.13, RN6.5 (R4.2)
N0_CLK_T: RN6.4 (R4.1), U6.15 (Y3)
N0_C_H: J4.11, RN6.8 (R1.2)
N0_C_T: RN6.1 (R1.1), U6.18 (Y0)
N0_D: U2.12 (GPIO9), U6.3 (A1)
N0_D_H: J4.12, RN6.7 (R2.2)
N0_D_T: RN6.2 (R2.1), U6.17 (Y1)
N0_E: U2.14 (GPIO10), U6.4 (A2)
N0_E_H: J4.8, RN6.6 (R3.2)
N0_E_T: RN6.3 (R3.1), U6.16 (Y2)
N0_G1: JP1.2 (C), U5.3 (A1)
N0_G1_H: J4.2, RN4.7 (R2.2)
N0_G1_T: RN4.2 (R2.1), U5.17 (Y1)
N0_G2: U2.6 (GPIO4), U5.6 (A4)
N0_G2_H: J4.6, RN5.8 (R1.2)
N0_G2_T: RN5.1 (R1.1), U5.14 (Y4)
N0_GP1: JP1.1 (A), U2.2 (GPIO1)
N0_GP15: JP1.3 (B), U2.20 (GPIO15)
N0_GP17: J7.13, U2.22 (GPIO17)
N0_GP18: J7.15, U2.24 (GPIO18)
N0_LAT: U2.16 (GPIO12), U6.6 (A4)
N0_LAT_H: J4.14, RN7.8 (R1.2)
N0_LAT_T: RN7.1 (R1.1), U6.14 (Y4)
N0_OE: R43.1, U2.17 (GPIO13), U6.7 (A5)
N0_OEB: Q1.3 (D), R40.1, U5.19 (G2), U6.19 (G2)
N0_OE_H: J4.15, R42.1, RN7.7 (R2.2)
N0_OE_T: RN7.2 (R2.1), U6.13 (Y5)
N0_R1: U2.1 (GPIO0), U5.2 (A0)
N0_R1_H: J4.1, RN4.8 (R1.2)
N0_R1_T: RN4.1 (R1.1), U5.18 (Y0)
N0_R2: U2.5 (GPIO3), U5.5 (A3)
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
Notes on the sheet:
ALIMENTATION — entrée 5 V 30 A, mesure du bus
DÉPARTS — un fusible et un bornier par dalle
ALIMENTATION DES PICO ET DES TAMPONS
TÊTE — Pico 2 W, liaisons L0 L1 L2, VSYNC, RDY
MESURE — analyseur logique ; fixations
NŒUD 0 — rangée du haut, dalles 7-8-9
NŒUD 1 — rangée du milieu, dalles 4-5-6
NŒUD 2 — rangée du bas, dalles 1-2-3
Liaisons : D0 D1 CLK CS sur GP 4k..4k+3 de la tête → GP19..GP22 du nœud k ; 33 Ω au départ (plan §2.6).
Diode Schottky par Pico : le bus ne remonte pas dans l'USB, un Pico en USB n'alimente pas le bus.
Cavalier JP : G1 sur GP1 (1-2) ou sur GP15 (2-3, Pico à GP1 mort). Sans Pico : tampons en haute impédance, dalle éteinte.

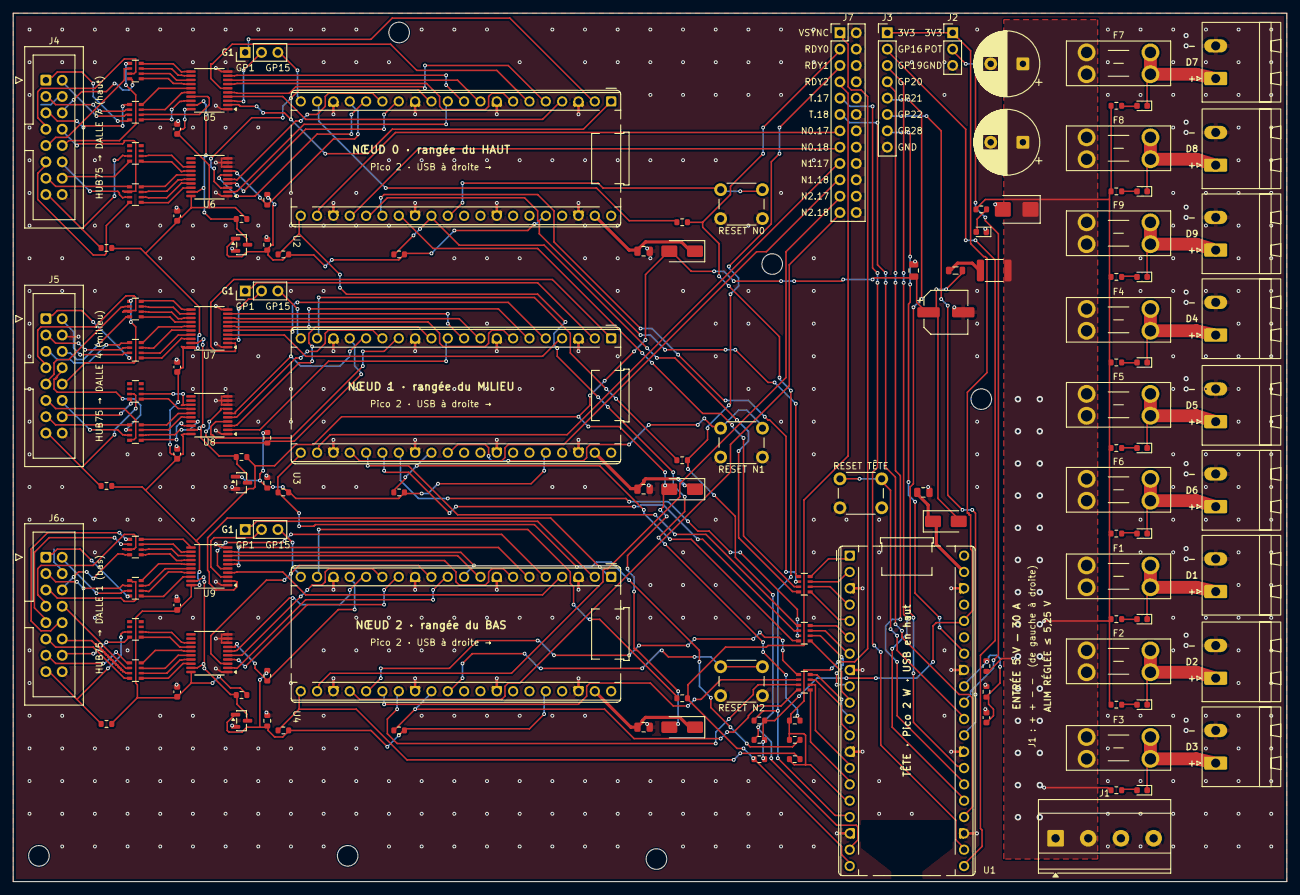
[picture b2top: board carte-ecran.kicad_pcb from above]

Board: 2 copper layers, 198.0 x 135.0 mm, 137 parts (0 on the bottom side), 220 nets.

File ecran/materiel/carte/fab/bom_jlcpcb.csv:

Comment,Designator,Footprint,LCSC Part #
SMBJ5.0A,D1,D_SMB,C83333
1k5 0603WAF1501T5E,R1,R_0603_1608Metric,C22843
"vert XL-1608PGC-06 (XINGLIGHT, vert émeraude)",LED1,LED_0603_1608Metric,C7371905
10k 0603WAF1002T5E,"R2,R3,R33,R34,R35,R40,R42,R43,R44,R45,R50,R52,R53,R54,R55,R60,R62,R63,R64,R65",R_0603_1608Metric,C25804
100n CC0603KRX7R9BB104,"C3,C20,C21,C22,C23,C24,C25",C_0603_1608Metric,C14663
1k 0603WAF1001T5E,"R11,R12,R13,R14,R15,R16,R17,R18,R19,R41,R51,R61",R_0603_1608Metric,C21190
rouge KT-0603R,"LED11,LED12,LED13,LED14,LED15,LED16,LED17,LED18,LED19",LED_0603_1608Metric,C2286
"0,75 A 1812L075/33DR (Littelfuse, 0,75 A maintien, 1,5 A déclenchement)",F10,Fuse_1812_4532Metric,C151170
"220 Ω 2 A BLM21PG221SN1D (220 Ω à 100 MHz, 2 A)",FB1,L_0805_2012Metric,C85840
"100µ 35V CK1V101M-CRE77 (100 µF 35 V, 6,3×7,7)",C4,CP_Elec_6.3x7.7,C19184138
10u CL21A106KAYNNNE,"C5,C6,C7,C8,C9",C_0805_2012Metric,C15850
SS14,"D2,D3,D4,D5",D_SMA,C2480
4×33 4D03WGJ0330T5E,"RN1,RN2,RN3,RN4,RN5,RN6,RN7,RN8,RN9,RN10,RN11,RN12,RN13,RN14,RN15",R_Array_Convex_4x0603,C25508
33 0603WAF330JT5E,"R30,R31,R32,R46,R56,R66",R_0603_1608Metric,C23140
74AHCT541 SN74AHCT541PWR,"U5,U6,U7,U8,U9,U10",TSSOP-20_4.4x6.5mm_P0.65mm,C50989
2N7002,"Q1,Q2,Q3",SOT-23,C8545
